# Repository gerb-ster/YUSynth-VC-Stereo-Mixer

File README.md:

# YUSynth-VC-Stereo-Mixer

This is my eurorack adaptation of the Mixout-VC Panner from YUSynth. I've ommited
the headphone out the VU meters. This is done because to compact the boards a bit
and to save space on the panels.

I've broken it up into 3 boards, one VoiceBoard for every channel, a mainboard 
containing the mixer and the Bass & Trebble and finally small daughter board for the
left/right output jacks.

The breaks up of the boards is done in such a way that you can decide for yourself
how many channels/voice you want to add.

The original design:
http://yusynth.net/Modular/EN/MIXOUT/index.html

## Status: (Almost) Finished

- done: first schematic & board design
- done: breadboard and test
- done: design frontpanel
- done: order PCB and build prototype
- todo: build frontpanel

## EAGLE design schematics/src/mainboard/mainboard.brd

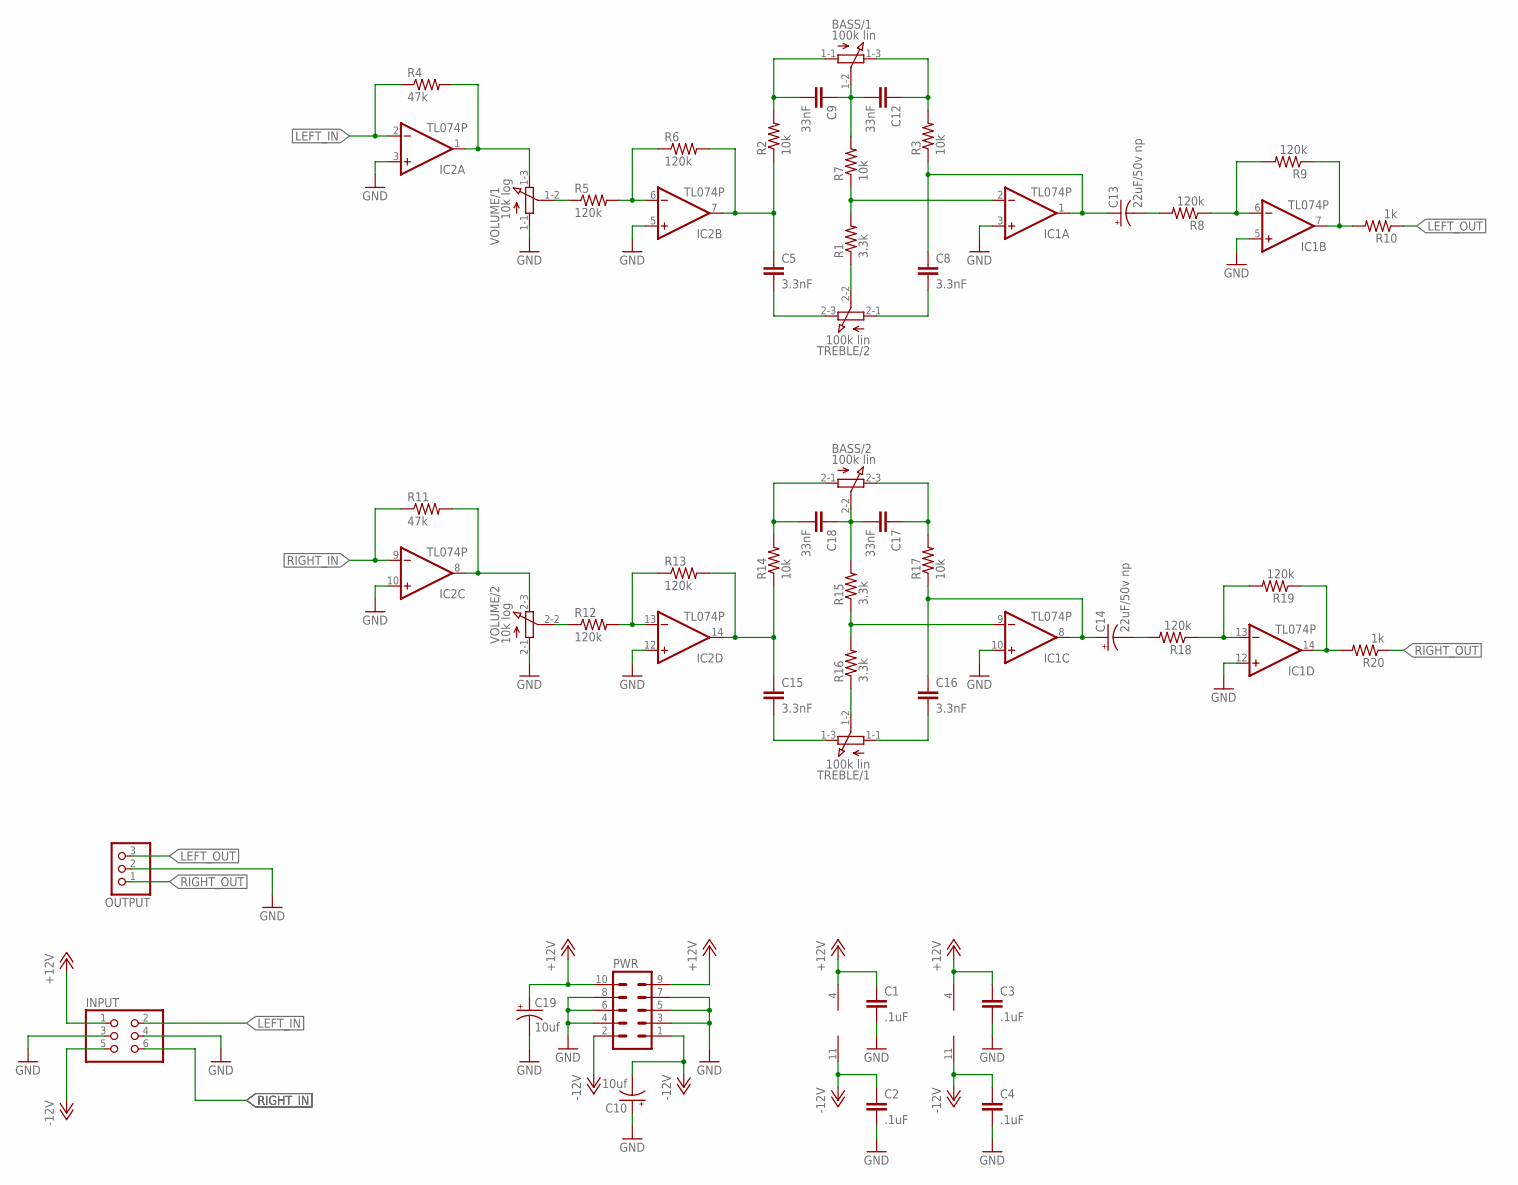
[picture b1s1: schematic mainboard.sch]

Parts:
BASS: 100k lin; 3RP/1610G
C1, C2, C3, C4: .1uF; C050-024X044
C5, C8, C15, C16: 3.3nF; C050-025X075
C9, C12, C17, C18: 33nF; C050-025X075
C10, C19: 10uf; E2,5-5
C13, C14: 22uF/50v np; E5-10,5
IC1, IC2: TL074P; DIL14
INPUT: PINHD-2X3/90; 2X03/90
OUTPUT: PINHD-1X3; 1X03
PWR: ML10
R1, R15, R16: 3.3k; 0207/7
R2, R3, R7, R14, R17: 10k; 0207/7
R4, R11: 47k; 0207/7
R5, R6, R8, R9, R12, R13, R18, R19: 120k; 0207/7
R10, R20: 1k; 0207/7
TREBLE: 100k lin; 3RP/1610G
VOLUME: 10k log; 3RP/1610G

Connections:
+12V: C1.1, C3.1, C19.+, IC1.4 (V+), IC2.4 (V+), INPUT.1, PWR.9, PWR.10
-12V: C2.1, C4.1, C10.-, IC1.11 (V-), IC2.11 (V-), INPUT.5, PWR.1, PWR.2
GND: C1.2, C2.2, C3.2, C4.2, C10.+, C19.-, IC1.3 (+IN), IC1.5 (+IN), IC1.10 (+IN), IC1.12 (+IN), IC2.3 (+IN), IC2.5 (+IN), IC2.10 (+IN), IC2.12 (+IN), INPUT.3, INPUT.4, OUTPUT.2, PWR.3, PWR.4, PWR.5, PWR.6, PWR.7, PWR.8, VOLUME.1-1 (A), VOLUME.2-1 (A)
LEFT_IN: IC2.2 (-IN), INPUT.2, R4.1
LEFT_OUT: OUTPUT.3, R10.1
unnamed: R5.1, VOLUME.1-2 (S)
unnamed: IC2.1 (OUT), R4.2, VOLUME.1-3 (E)
unnamed: IC2.6 (-IN), R5.2, R6.1
unnamed: C5.1, IC2.7 (OUT), R2.1, R6.2
unnamed: R1.1, TREBLE.2-2 (S)
unnamed: C5.2, TREBLE.2-3 (E)
unnamed: C8.2, TREBLE.2-1 (A)
unnamed: BASS.1-1 (A), C9.2, R2.2
unnamed: BASS.1-3 (E), C12.1, R3.2
unnamed: BASS.1-2 (S), C9.1, C12.2, R7.2
unnamed: IC1.2 (-IN), R1.2, R7.1
unnamed: C8.1, C13.+, IC1.1 (OUT), R3.1
unnamed: IC1.6 (-IN), R8.1, R9.2
unnamed: IC1.7 (OUT), R9.1, R10.2
unnamed: C13.-, R8.2
unnamed: C15.2, TREBLE.1-3 (E)
unnamed: IC2.8 (OUT), R11.2, VOLUME.2-3 (E)
unnamed: R12.1, VOLUME.2-2 (S)
unnamed: IC2.13 (-IN), R12.2, R13.1
unnamed: C16.2, TREBLE.1-1 (A)
unnamed: R16.1, TREBLE.1-2 (S)
unnamed: C15.1, IC2.14 (OUT), R13.2, R14.1
unnamed: IC1.9 (-IN), R15.1, R16.2
unnamed: BASS.2-2 (S), C17.2, C18.1, R15.2
unnamed: BASS.2-1 (A), C18.2, R14.2
unnamed: BASS.2-3 (E), C17.1, R17.2
unnamed: C14.-, R18.2
unnamed: C14.+, C16.1, IC1.8 (OUT), R17.1
unnamed: IC1.13 (-IN), R18.1, R19.2
unnamed: IC1.14 (OUT), R19.1, R20.2
RIGHT_IN: IC2.9 (-IN), INPUT.6, R11.1
RIGHT_OUT: OUTPUT.1, R20.1

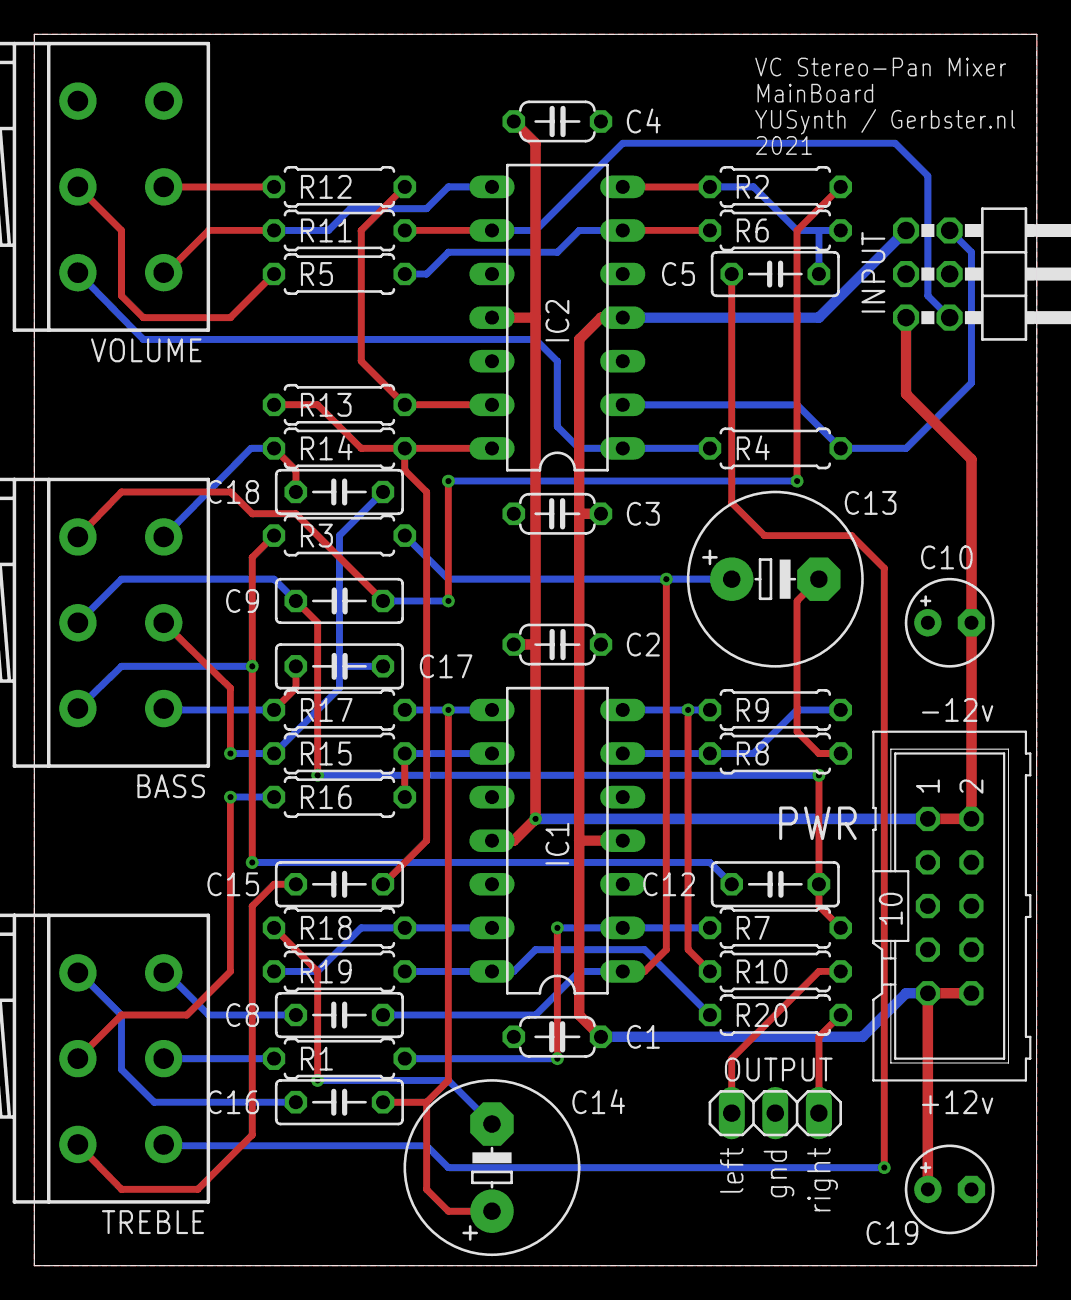
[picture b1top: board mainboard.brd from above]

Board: 2 copper layers, 58.4 x 71.8 mm, 44 parts (0 on the bottom side), 37 nets.

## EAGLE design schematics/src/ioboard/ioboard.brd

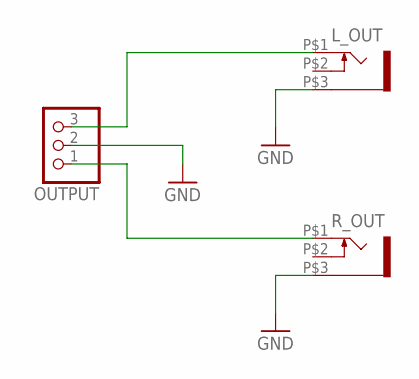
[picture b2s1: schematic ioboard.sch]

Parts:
L_OUT: WQP-PJ301M-12_JACK
OUTPUT: PINHD-1X3; 1X03
R_OUT: WQP-PJ301M-12_JACK

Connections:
GND: L_OUT.P$3 (1), OUTPUT.2, R_OUT.P$3 (1)
LEFT_OUT: L_OUT.P$1 (2), OUTPUT.3
RIGHT_OUT: OUTPUT.1, R_OUT.P$1 (2)

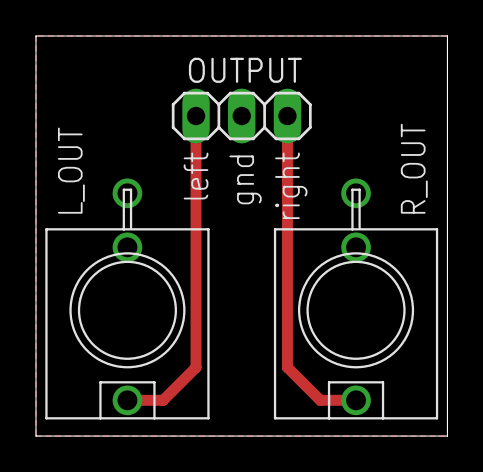
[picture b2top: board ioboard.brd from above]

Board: 2 copper layers, 22.9 x 22.2 mm, 3 parts (0 on the bottom side), 3 nets.

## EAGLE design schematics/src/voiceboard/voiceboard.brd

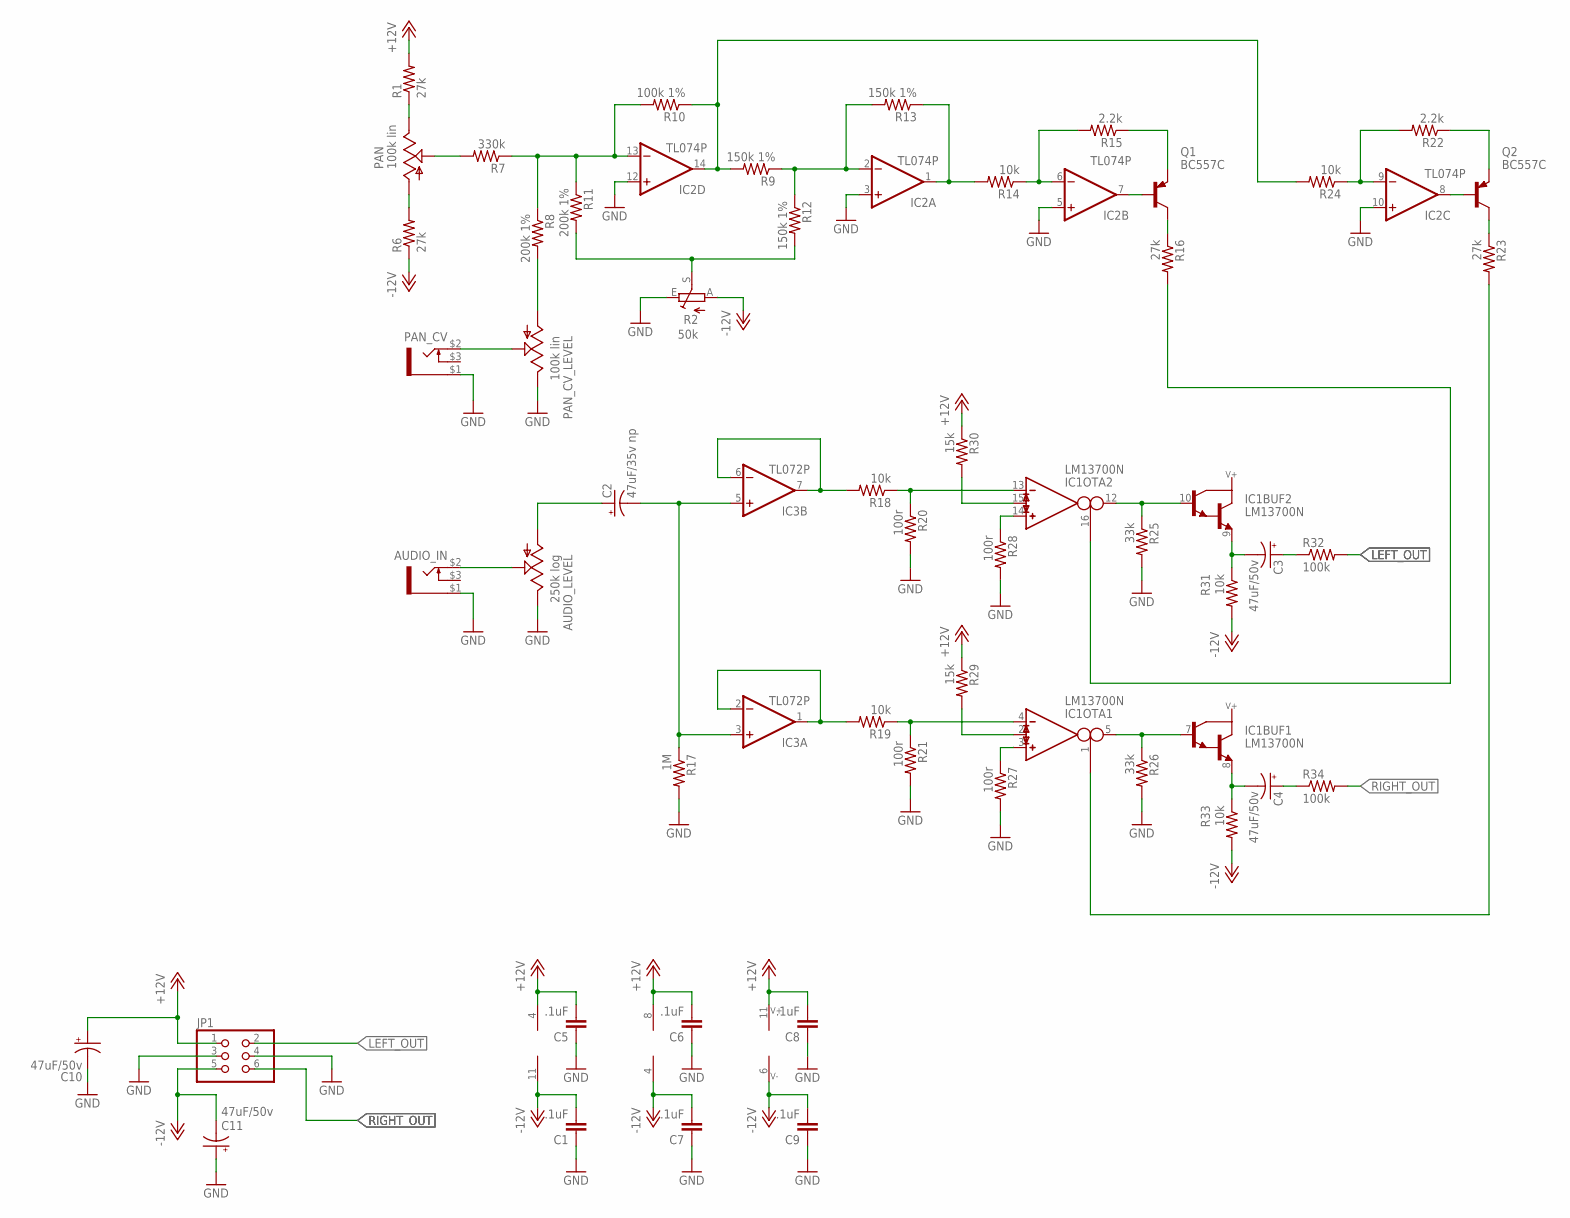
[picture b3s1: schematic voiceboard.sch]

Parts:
AUDIO_IN: PJ-323PJ-323; PJ-323
AUDIO_LEVEL: 250k log; EVUF
C1, C5, C6, C7, C8, C9: .1uF; C050-024X044
C2: 47uF/35v np; E5-10,5
C3, C4, C10, C11: 47uF/50v; E2,5-6
IC1: LM13700N; DIL16
IC2: TL074P; DIL14
IC3: TL072P; DIL08
JP1: PINHD-2X3/90; 2X03/90
PAN: 100k lin; EVUF
PAN_CV: PJ-323PJ-323; PJ-323
PAN_CV_LEVEL: 100k lin; EVUF
Q1, Q2: BC557C; TO92-EBC
R1, R6, R16, R23: 27k; 0207/7
R2: 50k; S64YW
R7: 330k; 0207/7
R8, R11: 200k 1%; 0207/7
R9, R12, R13: 150k 1%; 0207/7
R10: 100k 1%; 0207/7
R14, R18, R19, R24, R31, R33: 10k; 0207/7
R15, R22: 2.2k; 0207/7
R17: 1M; 0207/7
R20, R21, R27, R28: 100r; 0207/7
R25, R26: 33k; 0207/7
R29, R30: 15k; 0207/7
R32, R34: 100k; 0207/7

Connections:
+12V: C5.2, C6.2, C8.2, C10.+, IC1.11 (V+), IC2.4 (V+), IC3.8 (V+), JP1.1, R1.2, R29.1, R30.1
-12V: C1.2, C7.2, C9.2, C11.-, IC1.6 (V-), IC2.11 (V-), IC3.4 (V-), JP1.5, R2.A, R6.1, R31.2, R33.2
GND: AUDIO_IN.$1 (3), AUDIO_LEVEL.3 (E), C1.1, C5.1, C6.1, C7.1, C8.1, C9.1, C10.-, C11.+, IC2.3 (+IN), IC2.5 (+IN), IC2.10 (+IN), IC2.12 (+IN), JP1.3, JP1.4, PAN_CV.$1 (3), PAN_CV_LEVEL.3 (E), R2.E, R17.2, R20.2, R21.2, R25.2, R26.2, R27.2, R28.2
LEFT_OUT: JP1.2, R32.2
unnamed: PAN.3 (E), R1.1
unnamed: PAN.1 (A), R6.2
unnamed: PAN.2 (S), R7.2
unnamed: PAN_CV.$2 (1), PAN_CV_LEVEL.2 (S)
unnamed: IC2.13 (-IN), R7.1, R8.1, R10.2, R11.1
unnamed: IC2.14 (OUT), R9.2, R10.1, R24.2
unnamed: PAN_CV_LEVEL.1 (A), R8.2
unnamed: IC2.1 (OUT), R13.1, R14.2
unnamed: R2.S, R11.2, R12.2
unnamed: IC2.2 (-IN), R9.1, R12.1, R13.2
unnamed: IC2.6 (-IN), R14.1, R15.2
unnamed: IC2.7 (OUT), Q1.B
unnamed: Q1.C, R16.1
unnamed: Q1.E, R15.1
unnamed: AUDIO_IN.$2 (1), AUDIO_LEVEL.2 (S)
unnamed: AUDIO_LEVEL.1 (A), C2.+
unnamed: C2.-, IC3.3 (+IN), IC3.5 (+IN), R17.1
unnamed: IC3.1 (OUT), IC3.2 (-IN), R19.2
unnamed: IC3.6 (-IN), IC3.7 (OUT), R18.2
unnamed: IC1.4 (IN_N), R19.1, R21.1
unnamed: IC1.13 (IN_N), R18.1, R20.1
unnamed: IC2.8 (OUT), Q2.B
unnamed: IC2.9 (-IN), R22.2, R24.1
unnamed: Q2.E, R22.1
unnamed: Q2.C, R23.1
unnamed: IC1.10 (B), IC1.12 (OUT), R25.1
unnamed: IC1.5 (OUT), IC1.7 (B), R26.1
unnamed: IC1.14 (IN_P), R28.1
unnamed: IC1.3 (IN_P), R27.1
unnamed: IC1.15 (I_DIODE), R30.2
unnamed: IC1.2 (I_DIODE), R29.2
unnamed: C3.-, IC1.9 (E), R31.1
unnamed: C3.+, R32.1
unnamed: C4.-, IC1.8 (E), R33.1
unnamed: C4.+, R34.1
unnamed: IC1.16 (I_BIAS), R16.2
unnamed: IC1.1 (I_BIAS), R23.2
RIGHT_OUT: JP1.6, R34.2

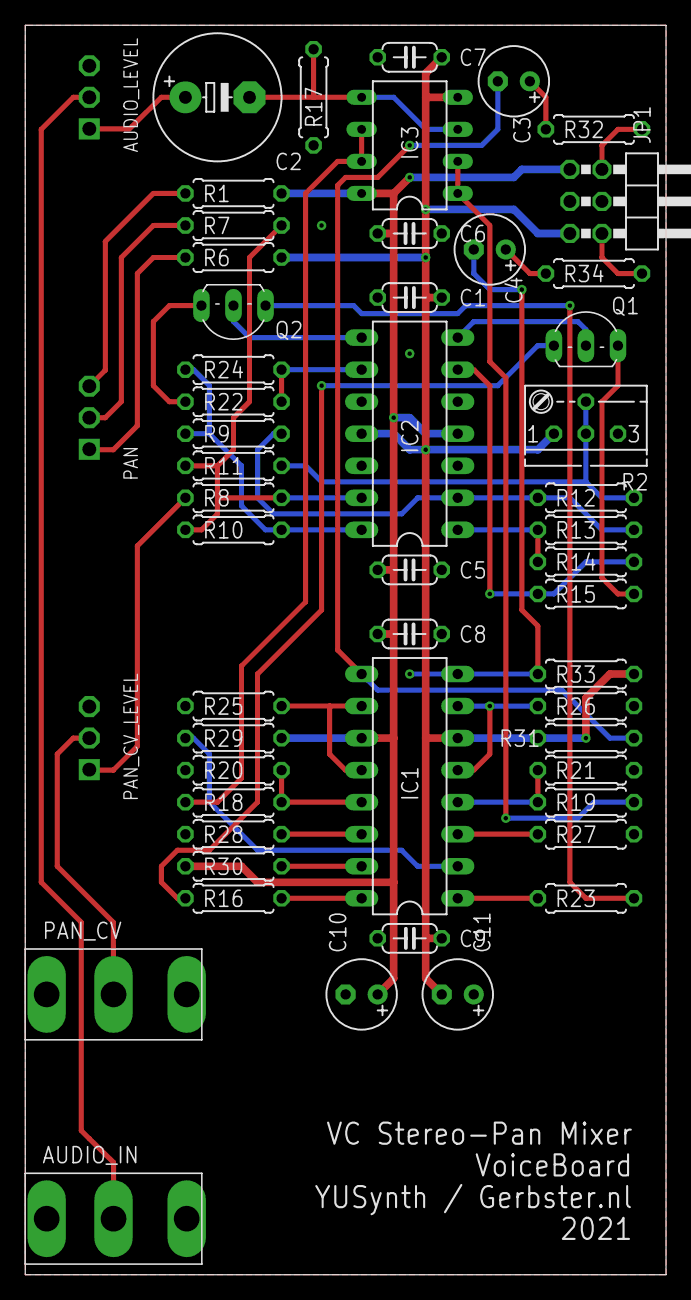
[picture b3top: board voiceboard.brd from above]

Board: 2 copper layers, 50.8 x 99.1 mm, 53 parts (0 on the bottom side), 42 nets.

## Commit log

2021-05-10 Added Status
2021-05-10 no message
2021-05-11 Added Status & Images
2021-05-11 add gitignore
2021-05-12 Added Faceplates
2021-06-15 Updated Schematics, Fixed Power Socket orientation
2021-07-19 Fixed minor issues, added documentation and updated some faceplates
2021-08-06 Updated some schematics and docs
2021-08-10 Fixed some bugs and updated documentation
2022-04-20 Some updates & bugfixes
2022-04-22 Fixed schematics & descriptions
2022-05-17 Updated Firmware
2022-05-18 Updated Faceplates
2022-05-18 Fixed issues
2022-05-21 Fixed schematics
2022-05-28 General updates
2022-06-13 Faceplates & Bugfixes
